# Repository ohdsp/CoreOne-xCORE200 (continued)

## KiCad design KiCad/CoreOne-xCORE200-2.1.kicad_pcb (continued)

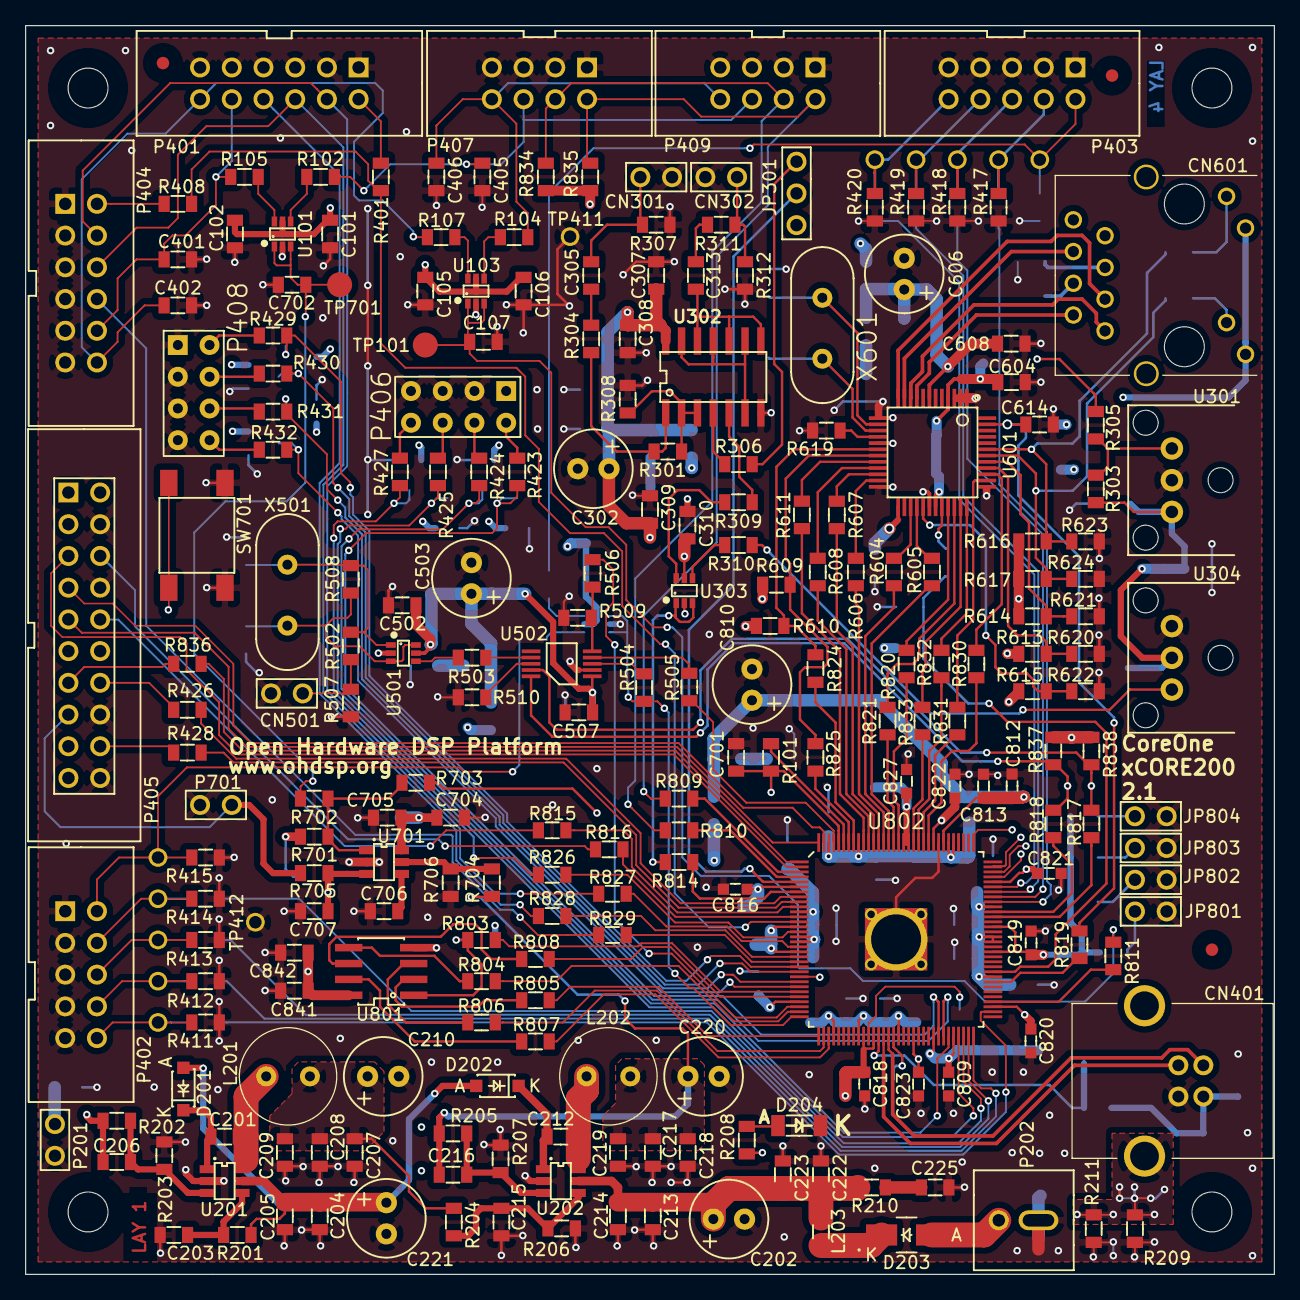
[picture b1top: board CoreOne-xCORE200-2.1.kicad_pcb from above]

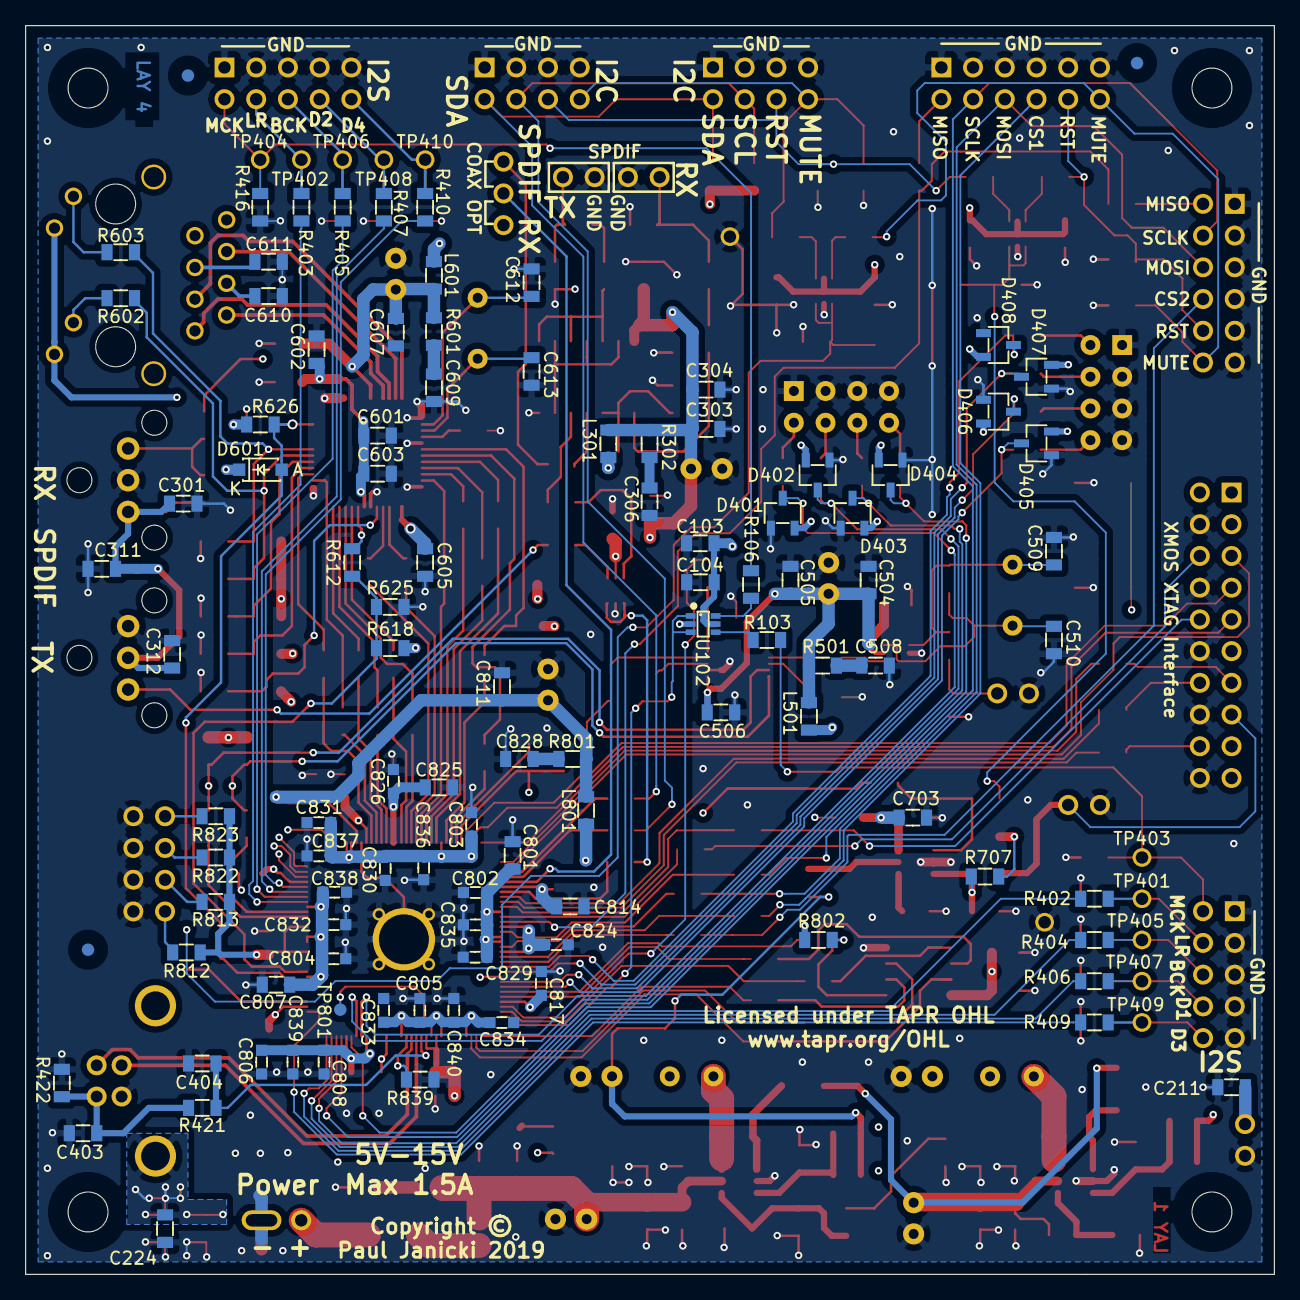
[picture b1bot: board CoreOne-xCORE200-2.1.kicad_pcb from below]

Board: 4 copper layers, 100.0 x 100.0 mm, 351 parts (114 on the bottom side), 213 nets.

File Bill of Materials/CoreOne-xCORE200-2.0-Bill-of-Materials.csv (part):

Reference; Quantity; Footprint; Value; Description; Size; Tolerance; Type; Voltage; Power; Current; Decription; 
C101 C103 C105 C307 C309 C311 C506 C614 C703 C842 ;10;SMD-0805;10u;'Ceramic capacitor;'0805;'20%;'X5R;'10V;';';';
C102 C104 C106 C201 C203 C205 C209 C211 C212 C214 C219 C223 C224 C301 C304 C305 C308 C310 C312 C313 C404 C502 C505 C507 C603 C604 C605 C608 C610 C611 C704 C841 ;32;SMD-0805;100n;'Ceramic capacitor;'0805;'10%;'X7R;'50V;';';';
C107 C215 C401 C402 C405 C406 C701 C702 C705 C706 C707 ;11;SMD-0805;10n;'Ceramic capacitor;'0805;'10%;'X7R;'50V;';';';
C202 C221 ;2;CAP-TH-D6.3mmP2.5mm;220u;'Aluminium electrolytic capacitor;';';'2.5mm pitch, 6.3mm diameter;'16V;';';';
C206 ;1;SMD-0805;39p;'Ceramic capacitor;'0805;'10%;'X7R;'50V;';';';
C207 C208 C217 C218 C303 C504 C607 C801 C807 C811 C814 C825 ;12;SMD-0805;22u;'Ceramic capacitor;'0805;'20%;'X5R;'10V;';';';
C210 C220 C302 C503 C606 C810 ;6;CAP-TH-D6.3mmP2.5mm;220u;'Low impedance aluminium electrolytic capacitor - Panasonic FC, FR or similar;';';'2.5mm pitch, 6.3mm diameter;'10V;';';';
C216 ;1;SMD-0805;N/F;'Ceramic capacitor;'0805;'10%;'X7R;'50V;';';';
C204 C213 C222 ;3;SMD-0805;22u;'Ceramic capacitor;'0805;'20%;'X5R;'25V;';';';
C225 C306 C508 C609 C828 ;5;SMD-0805;100p;'Ceramic capacitor;'0805;'5%;'C0G;'50V;';';';
C403 ;1;SMD-0805;2u2;'Ceramic capacitor;'0805;'10%;'X5R;'50V;';';';
C509 C510 C612 C613 ;4;SMD-0805;33p;'Ceramic capacitor;'0805;'5%;'NP0;'50V;';';';
C601 C602 ;2;SMD-0805;1u;'Ceramic capacitor;'0805;'10%;'X7R;'10V;';';';
C802 C803 C804 C805 C806 ;5;SMD-0603;1u;'Ceramic capacitor;'0603;'10%;'X7R;'10V;';';';
C808 C812 C816 C817 C818 C819 C820 C821 C822 C823 C824 C826 C829 C830 C831 C832 C833 C834 ;18;SMD-0603;100n;'Ceramic capacitor;'0603;'10%;'X7R;'50V;';';';
C809 C813 C827 C835 C836 C837 C838 C839 C840 ;9;SMD-0603;10n;'Ceramic capacitor;'0603;'10%;'X7R;'50V;';';';
CN301 CN302 CN501 ;3;CONN_SIL_2_1MM;COAX;'1x2 2.54mm pitch pin header - use with 75Ohm coax;';';';';';';';
CN401 ;1;CONN-USB-B-61729-0010;CONN-USB-B-61729;'USB B Connector - Amphenol 61729 Series - eg: 61729-0010;';';';';';';';
CN601 ;1;CONN-RJ45-ARJC02-111xxxx;ARJC02-111009D;'ARCJ02 series RJ45 connector with LED - ARJC02-111009D;';';';';';';';
D201 D202 D601 ;3;DIODE-SOD-123;1N4148W-7-F;'Text description;';';';';';';';
D203 ;1;DIODE-SMA;B240A;'B240A 2A 40V Schottky Rectifier - SMA (DO-214AC);';';';';';';';
D204 ;1;SMD-1206;Green LED 1206;'Green LED - SMD - Vf 1.8V to 2.2V;'1206;';';';';';';
D401 D402 D403 D404 D405 D406 D407 D408 ;8;IC-SOT23;BAV99;'100V 150mA Small Signal Switching Diode, Dual in Series;';';';';';';';
FID201 FID202 FID203 FID204 FID205 FID206 ;6;FID-1MM-3MM;MNT_HOLE;'Fiducial;';';';';';';';
JP301 ;1;CONN_SIL_3_1MM;CONN_3x1;'1x3 2.54mm pitch pin header;';';';';';';';
L201 ;1;IND-TH-DR0608;DR0608-153L;'Coilcraft DR0608-153L DCR=0.052Ohm Isat=2.7A Irms=2.7A;';';';';';'2.7A;';
L202 ;1;IND-TH-DR0608;DR0608-332L;'Coilcraft DR0608-332L DCR=0.012Ohm Isat=5.3A Irms=5.0A;';';';';';'5.3A;';
L203 ;1;SMD-0805;600R@100MHz;'Ferrite bead, current rating 2A or higher, 600R@100MHz;'0805;';';';';'=>2A;';
L301 L501 L601 L801 ;4;SMD-0805;600R@100MHz;'Ferrite bead, current rating 1A or higher, 600R@100MHz;'0805;';';';';'=>1A;';
MNT201 MNT202 MNT203 MNT204 ;4;MNT_HOLE_3.2mm;MNT_HOLE;'Mounting hole;';';';';';';';
JP801 JP802 JP803 JP804 P201 P701 ;6;CONN_SIL_2_1MM;CONN_2x1;'1x2 2.54mm pitch pin header;';';';';';';';
P202 ;1;CONN-2WAY-2.54mm-3.81mm-SPACING;CONN_2x1;'2 way screw terminal, any 2.54mm to 3.81mm pitch part;';';';';';';';
P401 P404 ;2;CONN_DIL_2X6_BOX_1MM;CONN_02X06;'2x6 2.54mm pitch box header;';';';';';';';
P402 P403 ;2;CONN_DIL_2X5_BOX_1MM;CONN_02X05;'2x5 2.54mm pitch box header;';';';';';';';
P405 ;1;CONN_DIL_2X10_BOX_1MM;CONN_02X10;'2x10 2.54mm pitch box header;';';';';';';';
P406 P408 ;2;CONN_DIL_2X04;CONN_02X04;'2x4 2.54mm pitch pin header;';';';';';';';
P407 P409 ;2;CONN_DIL_2X4_BOX_1MM;CONN_02X04;'2x4 2.54mm pitch box header;';';';';';';';
R101 R401 R402 R403 R404 R405 R406 R407 R408 R409 R410 R426 R428 R803 R804 R805 R806 R807 R808 R809 R810 R814 R817 R818 R824 R825 ;26;SMD-0805;0;'Thick or thin film resistor;'0805;'1%;';';'100mW;';';
R102 R103 R104 R105 R106 R107 R604 R605 R606 R607 R608 R611 R612 R811 R815 R816 R819 R820 R821 R826 R827 R828 R829 R830 R831 R832 R833 R836 ;28;SMD-0805;33;'Thick or thin film resistor;'0805;'1%;';';'100mW;';';
R201 R202 R206 ;3;SMD-0805;100k;'Thick or thin film resistor;'0805;'1%;';';'100mW;';';
R203 ;1;SMD-0805;22k;'Thick or thin film resistor;'0805;'1%;';';'100mW;';';
R204 ;1;SMD-0805;75k;'Thick or thin film resistor;'0805;'1%;';';'100mW;';';
R205 R301 R303 R308 R421 R626 R802 ;7;SMD-0805;10k;'Thick or thin film resistor;'0805;'1%;';';'100mW;';';
R207 R704 ;2;SMD-0805;15k;'Thick or thin film resistor;'0805;'1%;';';'100mW;';';
R208 R602 R603 ;3;SMD-0805;220;'Thick or thin film resistor;'0805;'1%;';';'100mW;';';
R209 R211 ;2;SMD-0805;10;'Thick or thin film resistor;'0805;'1%;';';'100mW;';';
R210 R302 R501 R601 R801 ;5;SMD-0805;47;'Thick or thin film resistor;'0805;'1%;';';'100mW;';';
R304 R702 R703 R705 ;4;SMD-0805;100;'Thick or thin film resistor;'0805;'1%;';';'100mW;';';
R305 R306 R307 R309 R310 ;5;SMD-0805;75;'Thick or thin film resistor;'0805;'1%;';';'100mW;';';
R311 ;1;SMD-0805;360;'Thick or thin film resistor;'0805;'1%;';';'100mW;';';
R312 ;1;SMD-0805;91;'Thick or thin film resistor;'0805;'1%;';';'100mW;';';
R411 R412 R413 R414 R415 R416 R417 R418 R419 R420 R502 R506 R507 R613 R614 R615 R623 R624 R625 R834 R835 ;21;SMD-0805;N/F;'Thick or thin film resistor;'0805;'1%;';';'100mW;';';
R422 ;1;SMD-0805;47k;'Thick or thin film resistor;'0805;'1%;';';'100mW;';';
R423 R424 R425 R427 R429 R430 R431 R432 R510 R609 R610 R618 R620 R621 R622 R812 R813 R822 R823 ;19;SMD-0805;1k;'Thick or thin film resistor;'0805;'1%;';';'100mW;';';
R503 R504 R505 ;3;SMD-0805;33R;'Thick or thin film resistor;'0805;'1%;';';'100mW;';';
R508 ;1;SMD-0805;1Meg;'Thick or thin film resistor;'0805;'1%;';';'100mW;';';
R509 ;1;SMD-0805;0R;'Thick or thin film resistor;'0805;'1%;';';'100mW;';';
R616 R617 ;2;SMD-0805;4k7;'Thick or thin film resistor;'0805;'1%;';';'100mW;';';
R619 ;1;SMD-0805;6K49;'Thick or thin film resistor;'0805;'1%;';';'100mW;';';
R701 R707 R837 R838 ;4;SMD-0805;2k2;'Thick or thin film resistor;'0805;'1%;';';'100mW;';';
R706 ;1;SMD-0805;10k7;'Thick or thin film resistor;'0805;'1%;';';'100mW;';';
R839 ;1;SMD-0805;43R2;'Thick or thin film resistor;'0805;'1%;';';'100mW;';';
SW701 ;1;SW_TACT_SMD;SWITCH;'6mm x 6mm SMD tactile switch - e.g. TE FSM2JSMA;';';';';';';';
TP101 TP701 ;2;TP-2mm;PIN;
TP401 TP402 TP403 TP404 TP405 TP406 TP407 TP408 TP409 TP410 TP411 TP412 ;12;TP-TH-1mm;PIN;
TP801 ;1;TP-1mm;PIN;'Text description;';';';';';';';
U101 U102 U103 ;3;IC-SC70-6;NC7WZ16P6X;
U201 U202 ;2;IC-SOT23-6;RT7285C;'Richtek RT7285C 1.5A 18V Step Down Converter;';';';';';';';
U301 ;1;IC_SPDIF_OPTO;IC-SPDIF-RX-OPTO;'TOSLINK receiver e.g. CLIFF FC684205R;';';';';';';';
U302 ;1;IC_SOIC_14;74HC04;'74HC04 Hex Inverter - SOIC-14;';';';';';';'74HC04 Hex Inverter - SOIC-14;
U303 ;1;IC-SC70-6;NC7WZ16P6X;'UHS Dual Buffer;';';';';';';';
U304 ;1;IC_SPDIF_OPTO;IC-SPDIF-TX-OPTO;'TOSLINK transmitter e.g. CLIFF FC684205T;';';';';';';';
U501 ;1;IC-SC70-6;NC7WZ04P6X;'NC7WZ04 TinyLogic UHS Dual Inverter;';';';';';';';
U502 ;1;IC-MSOP-10;CS2200-CP;'Cirrus Logic CS2200-CP Fractional-N Frequency Synthesizer;';';';';';';';
U601 ;1;IC-LQFP48_7x7;KSZ8081MLX;'Microchip KSZ8081MLXCA LQFP-48 10Base-T/100Base-TX Ethernet PHY;';';';';';';';
U701 ;1;IC-SOT23-6;NCP308;'On Semi NCP308 SOT-23-6 TSOP-6 Supervisor;';';';';';';';
U801 ;1;IC_SOIC_8;IC-FLASH-SPI;'SPI/Quad SPI Flash Memory - SOIC 8 - For use with XE-216-TQ128, XEF216-512-TQ128 has internal flash;';';';';';';';
U802 ;1;IC-TQ128-XMOS-HF;XE216-512-TQ128;'XMOS 200 XE216-512-TQ128 Microcontroller;';';';';';';';
X501 ;1;XTAL_HC49_TH;24M000;'HC49 24.000MHz Crystal – 30ppm or better – 18pF;';';';';';';';
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
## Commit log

2019-04-02 CoreOne-xCORE200-2.0
    CoreOne-xCORE200-2.0
2019-04-04 CoreOne-xCORE200-2.1
    CoreOne-xCORE200-2.1
    Improved grounding on power connector
2019-04-04 Revert "CoreOne-xCORE200-2.0"
    This reverts commit ef9318669a1c13780c7fcf0a8911ea6c14e73c30.
2019-04-04 CoreOne-xCORE200-2.1
    CoreOne-xCORE200-2.1
